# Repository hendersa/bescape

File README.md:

# bescape
Beagle Entertainment System hardware cape files for EAGLE PCB

The BESCape is a BeagleBone Black cape board designed to be used with
the Beagle Entertainment System (http://beaglesnes.org) software system.
BESCape is a hardware interface that provides the BES software with a
DS1307 battery-backed RTC and two Super Nintendo controller connectors. 
This allows a BeagleBone Black running BES to more effectively serve as
a retrogaming console.

The cape uses the following pins:

1. P8.01: GND       (Grounding plane)
2. P8.02: GND       (Grounding plane)
3. P8.26: GPIO1_29  (GPIO for Gamepad2 DATA signal)
4. P9.01: GND       (Grounding plane)
5. P9.02: GND       (Grounding plane)
6. P9.03: VDD_3V3   (3.3VDC to gamepad line-level converter FETs)
7. P9.04: VDD_3V3   (3.3VDC to RTC and EEPROM)
8. P9.05: VDD_5V    (5.0VDC to gamepad line-level converter FETs)
9. P9.06: VDD_5V    (5.0VDC to gamepad line-level converter FETs)
10. P9.11: UART4_RXD (GPIO for Gamepad1/2 CLOCK signal)
11. P9.12: GPIO1_28  (GPIO for Gamepad1 DATA signal)
12. P9.13: UART4_TXD (GPIO for Gamepad1/2 LATCH signal)
13. P9.17: I2C1_SCL  (I2C SCL for RTC)
14. P9.18: I2C1_SDA  (I2C SDA for RTC)
15. P9.19: I2C2_SCL  (I2C SCL for cape EEPROM)
16. P9.20: I2C2_SDA  (I2C SDA for cape EEPROM)
17. P9.22: UART2_RXD (GPIO for menu/pause switch signal)
18. P9.27: GPIO3_19  (GPIO for menu/pause LED)
19. P9.43: GND       (Grounding plane)
20. P9.44: GND       (Grounding plane)
21. P9.45: GND       (Grounding plane)
22. P9.46: GND       (Grounding plane)

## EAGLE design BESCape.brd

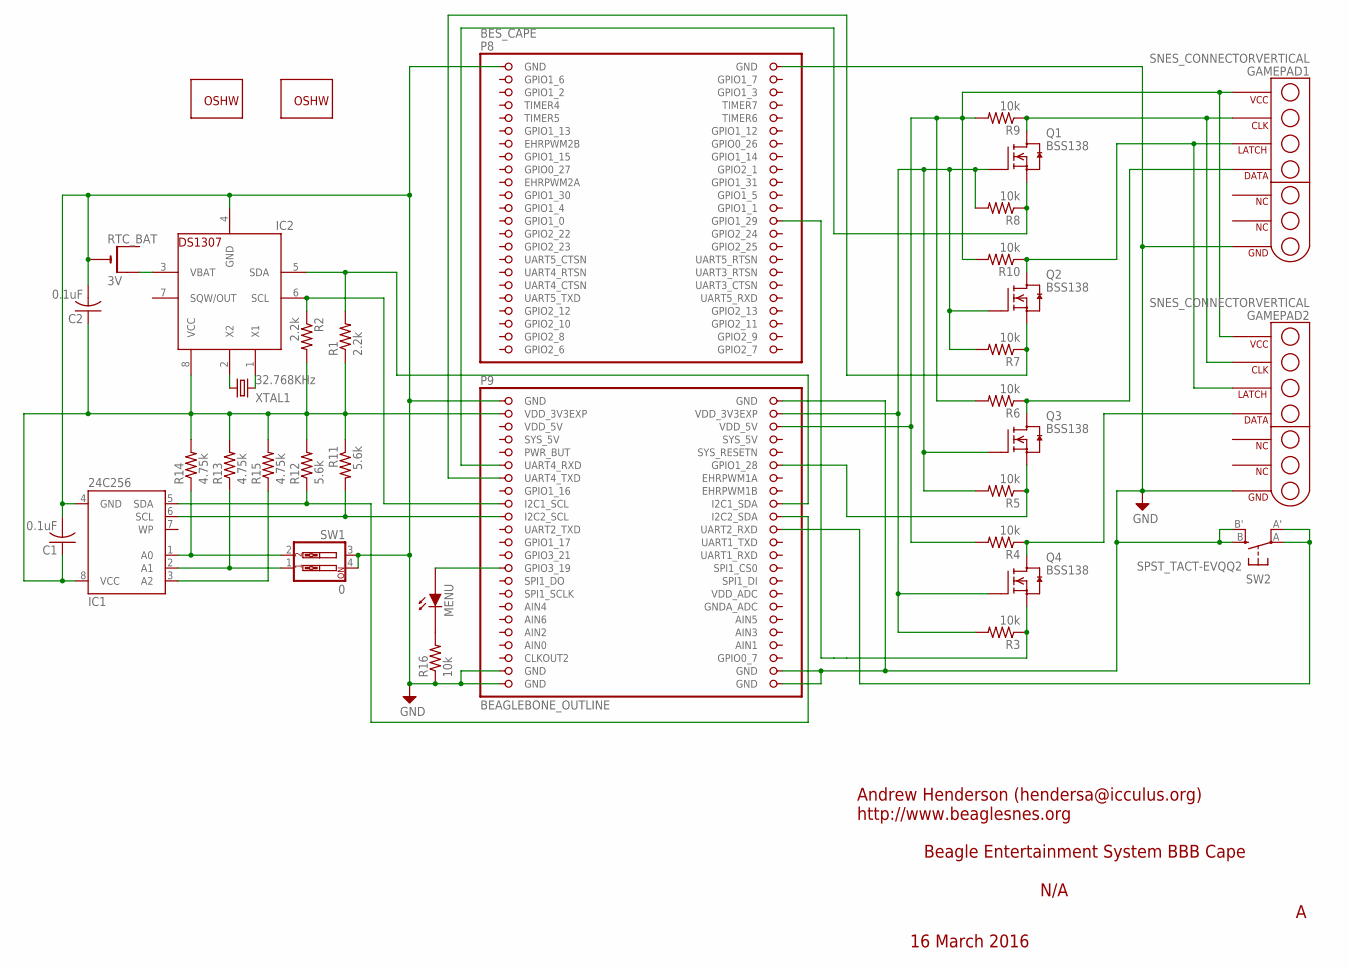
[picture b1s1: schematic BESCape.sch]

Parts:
BES_CAPE: BEAGLEBONE_OUTLINE; BEAGLEBONE_SHIELD
C1, C2: 0.1uF; C0805
GAMEPAD1, GAMEPAD2: SNES_CONNECTORVERTICAL; SNES_CONNECTOR_VERTICAL
GOLD_ORB_SM1: OSHWLOGO_GOLD_ORB_LG; OSHW0
GOLD_ORB_SM3: OSHWLOGO_GOLD_ORB_SM; OSHW2
IC1: 24C256; DIL08
IC2: DS1307; DIL08
MENU: LEDD; 1206P
Q1, Q2, Q3, Q4: BSS138; SOT23
R1, R2: 2.2k; R0805
R3, R4, R5, R6, R7, R8, R9, R10, R16: 10k; R0805
R11, R12: 5.6k; R0805
R13, R14, R15: 4.75k; R0805
RTC_BAT: 3V; CR1220-SMD
SW1: 0; DIPSWITCH-02
SW2: SPST_TACT-EVQQ2; EVQ-Q2
XTAL1: 32.768KHz; TC38H

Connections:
AIN0: BES_CAPE.85 (AIN0)
GND: BES_CAPE.1 (GND), BES_CAPE.2 (GND), BES_CAPE.47 (GND), BES_CAPE.48 (GND), BES_CAPE.89 (GND), BES_CAPE.90 (GND), BES_CAPE.91 (GND), BES_CAPE.92 (GND), C1.2, C2.2, GAMEPAD1.P$17 (GND), GAMEPAD2.P$17 (GND), IC1.4 (GND), IC2.4 (GND), R16.1, RTC_BAT.-, SW1.3, SW1.4, SW2.B (S), SW2.B' (S1)
unnamed: BES_CAPE.26 (GPIO1_29), Q4.2 (S), R3.1
unnamed: MENU.2 (D_OUT), R16.2
unnamed: BES_CAPE.73 (GPIO3_19), MENU.1 (D_IN)
unnamed: BES_CAPE.64 (I2C1_SDA), IC2.5 (SDA), R1.2
unnamed: GAMEPAD1.P$13 (LATCH), GAMEPAD2.P$13 (LATCH), Q2.3 (D), R10.1
unnamed: IC2.2 (X2), XTAL1.1
unnamed: IC2.1 (X1), XTAL1.2
unnamed: GAMEPAD1.P$12 (CLK), GAMEPAD2.P$12 (CLK), Q1.3 (D), R9.1
unnamed: BES_CAPE.58 (GPIO1_28), Q3.2 (S), R5.1
unnamed: BES_CAPE.59 (UART4_TXD), Q2.2 (S), R7.1
unnamed: BES_CAPE.68 (UART2_RXD), SW2.A, SW2.A' (P1)
unnamed: IC1.3 (A2), R15.1
unnamed: IC1.2 (A1), R13.1, SW1.1
unnamed: BES_CAPE.63 (I2C1_SCL), IC2.6 (SCL), R2.1
unnamed: GAMEPAD2.P$14 (DATA), Q4.3 (D), R4.1
unnamed: GAMEPAD1.P$14 (DATA), Q3.3 (D), R6.1
unnamed: IC1.1 (A0), R14.1, SW1.2
unnamed: BES_CAPE.65 (I2C2_SCL), IC1.6 (SCL), R11.2
unnamed: BES_CAPE.66 (I2C2_SDA), IC1.5 (SDA), R12.1
PRU_CLOCK: BES_CAPE.57 (UART4_RXD), Q1.2 (S), R8.1
SYS_5V: BES_CAPE.53 (SYS_5V)
VBAT: IC2.3 (VBAT), RTC_BAT.+$2 (+1)
VCC: BES_CAPE.49 (VDD_3V3EXP), C1.1, C2.1, IC1.8 (VCC), IC2.8 (VCC), R1.1, R2.2, R11.1, R12.2, R13.2, R14.2, R15.2
VDD_3V3EXP: BES_CAPE.50 (VDD_3V3EXP), Q1.1 (G), Q2.1 (G), Q3.1 (G), Q4.1 (G), R3.2, R5.2, R7.2, R8.2
VDD_5V: BES_CAPE.51 (VDD_5V), BES_CAPE.52 (VDD_5V), GAMEPAD1.P$11 (VCC), GAMEPAD2.P$11 (VCC), R4.2, R6.2, R9.2, R10.2

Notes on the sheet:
Andrew Henderson (hendersa@icculus.org) http://www.beaglesnes.org
N/A
Beagle Entertainment System BBB Cape
16 March 2016

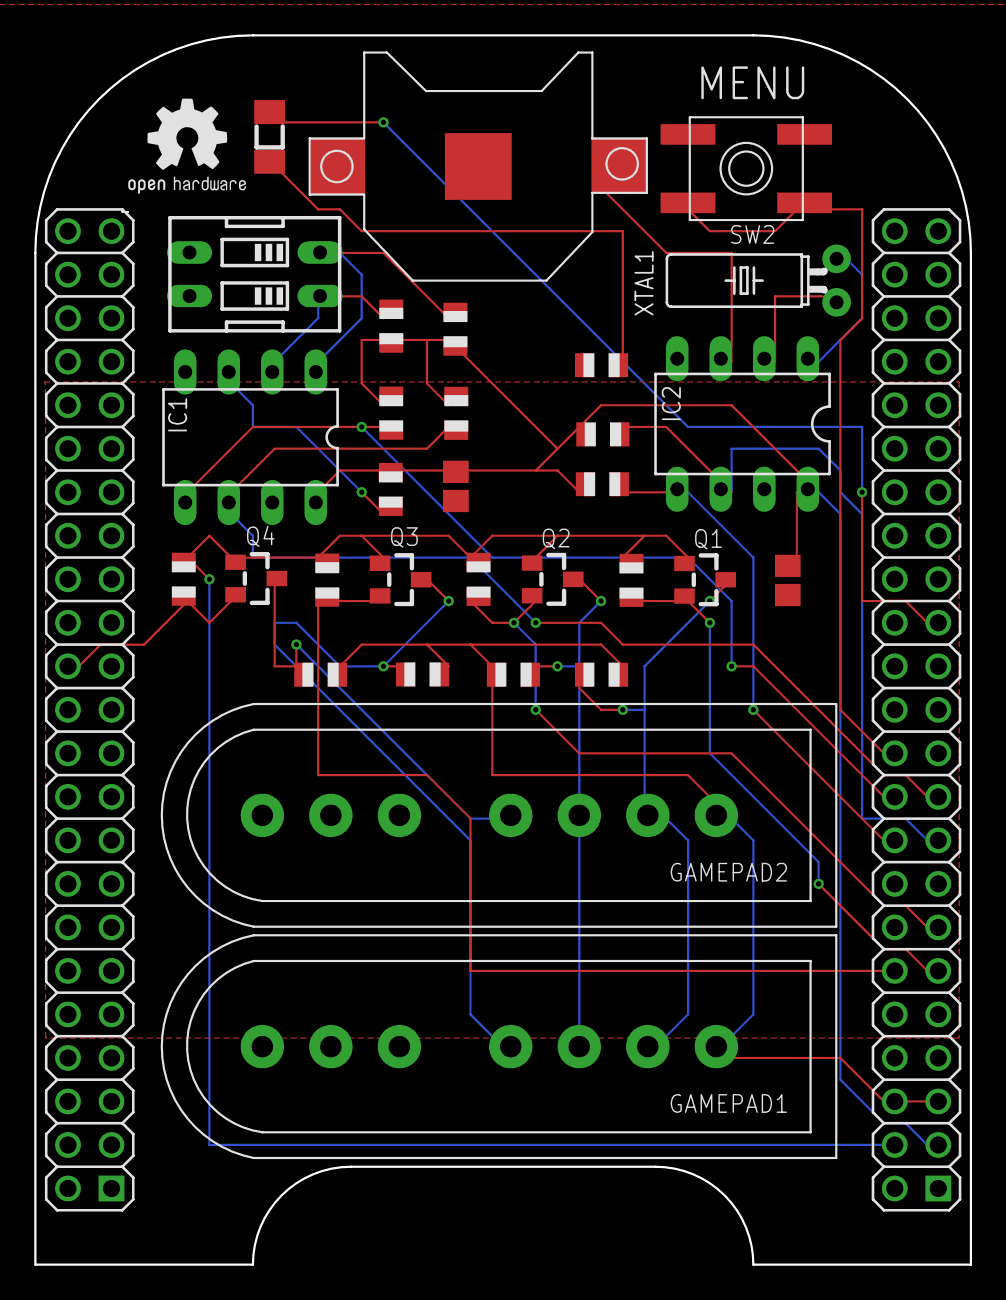
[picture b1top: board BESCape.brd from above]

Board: 2 copper layers, 54.6 x 71.8 mm, 34 parts (1 on the bottom side), 25 nets.

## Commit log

2016-03-17 Initial import of current PCB design
2016-03-17 Reformat of readme

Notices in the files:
BESCape.brd:
(C) 2016 Andrew Henderson
parts and their libraries:
m-pad-2.1: License : GNU General Public License version 2 (see bottom)
SparkFun-Electromechanical: Licensing: Creative Commons ShareAlike 4.0 International - https://creativecommons.org/licenses/by-sa/4.0
